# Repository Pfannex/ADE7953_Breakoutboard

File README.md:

# ADE7953 MQTT Wattmeter

Der ADE7953 wird über einen ESP8266-WLAN-Controller per I²C angesteuert.
Aktuell gibt es nur ein Breakoutboard mit Grundbeschaltung. 
Die Ankopplung der Leistungsmessgrößen erfolgt zu einem späteren Zeitpunkt.

***

- **ADE7953**
  - [Kalibrierung](https://github.com/Pfannex/ADE7953_Breakoutboard/wiki/Kalibrierung-%7C-ADE7953-MQTT-Wattmeter)
- **Firmware**
  - [ESP8266-Web-Interface](https://github.com/Pfannex/ADE7953_Breakoutboard/wiki/ESP8266-Web-Interface-%7C-ADE7953-MQTT-Wattmeter)
  - [MQTT](https://github.com/Pfannex/ADE7953_Breakoutboard/wiki/MQTT-%7C-ADE7953-MQTT-Wattmeter)
  - [FileSystem](https://github.com/Pfannex/ADE7953_Breakoutboard/wiki/FileSystem-%7C-ADE7953-MQTT-Wattmeter)
  - [OTA](https://github.com/Pfannex/ADE7953_Breakoutboard/wiki/OTA-%7C-ADE7953-MQTT-Wattmeter)
- **FHEM**
  - [FHEM](https://github.com/Pfannex/ADE7953_Breakoutboard/wiki/FHEM-%7C-ADE7953-MQTT-Wattmeter)  
  
***
[ToDo](https://github.com/Pfannex/ADE7953_Breakoutboard/blob/master/ToDo.md)

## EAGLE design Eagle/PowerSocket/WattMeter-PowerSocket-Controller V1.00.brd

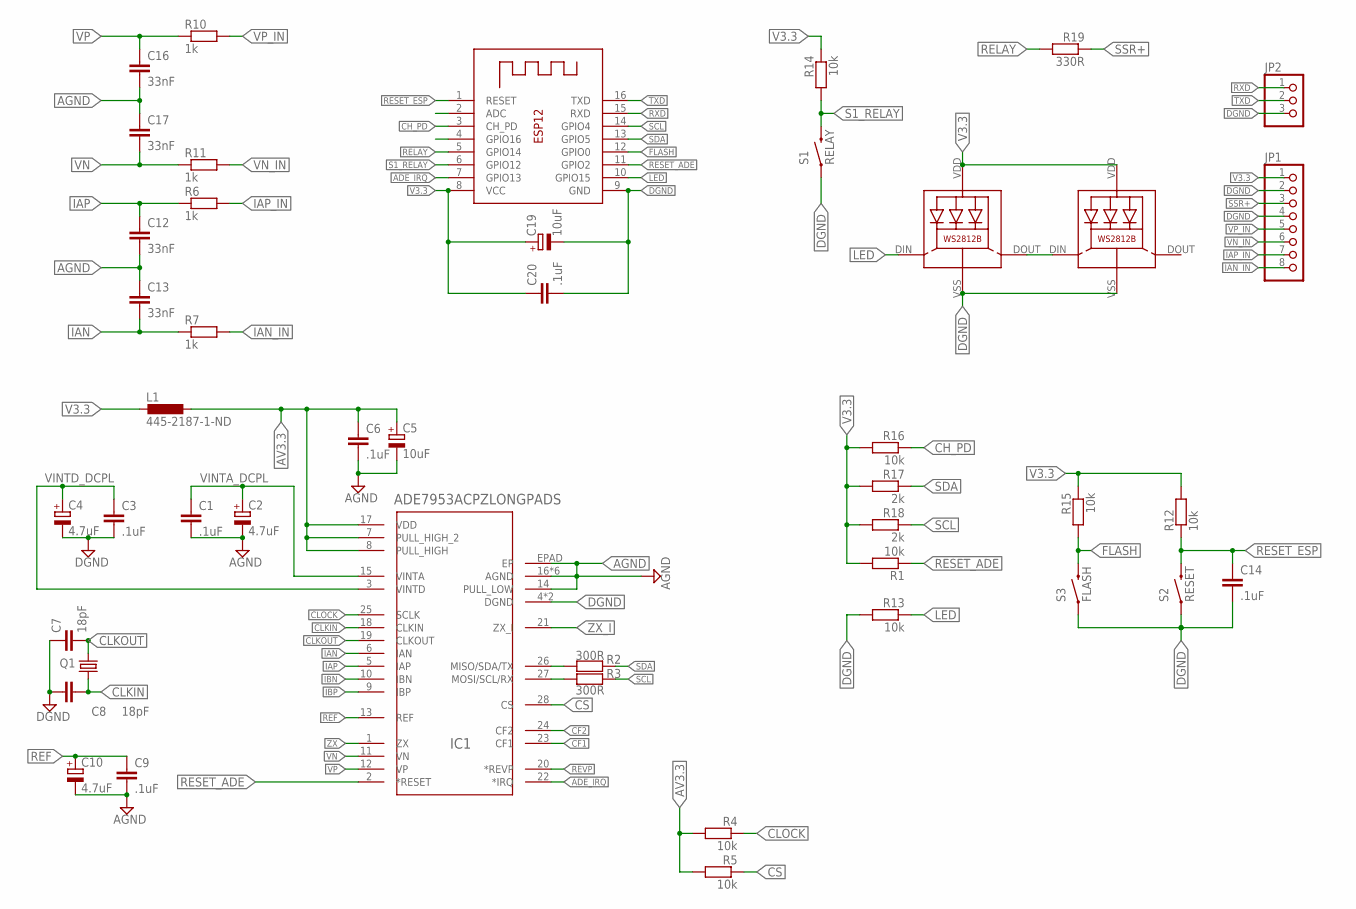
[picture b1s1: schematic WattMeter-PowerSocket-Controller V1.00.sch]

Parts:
C1, C3, C6, C9, C14, C20: .1uF; C0805K@1
C2, C4, C10: 4.7uF; A/3216-18R
C5, C19: 10uF; A/3216-18R
C7, C8: 18pF; C0805K@1
C12, C13, C16, C17: 33nF; C0805K@1
IC1: ADE7953ACPZLONGPADS; VQFN-28-D
JP1: PINHD-1X8; 1X08
JP2: PINHD-1X3; 1X03
L1: 445-2187-1-ND; L2012C
LED1, LED2: WS2812B
Q1: 535-10200-1-ND; SM49
R1, R4, R5, R12, R13, R14, R15, R16: 10k; R0805@1
R2, R3: 300R; R0805@1
R6, R7, R10, R11: 1k; R0805@1
R17, R18: 2k; R0805@1
R19: 330R; R0805@1
S1: RELAY; TACTILE-SWITCH-SMD
S2: RESET; TACTILE-SWITCH-1101NE
S3: FLASH; TACTILE-SWITCH-1101NE
X1: ESP-12

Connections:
ADC: X1.2 (ADC)
ADE_IRQ: IC1.22 (*IRQ), X1.7 (GPIO13)
AGND: C1.2, C2.-, C5.-, C6.2, C9.2, C10.-, C12.2, C13.1, C16.2, C17.1, IC1.14 (PULL_LOW), IC1.16 (AGND), IC1.29 (AGND), IC1.30 (AGND), IC1.31 (AGND), IC1.32 (AGND), IC1.EPAD (EP), IC1._AGND (AGND)
AV3.3: C5.+, C6.1, IC1.7 (PULL_HIGH_2), IC1.8 (PULL_HIGH), IC1.17 (VDD), L1.1, R4.2, R5.2
CF1: IC1.23 (CF1)
CF2: IC1.24 (CF2)
CH_PD: R16.1, X1.3 (CH_PD)
CLKIN: C8.2, IC1.18 (CLKIN), Q1.1
CLKOUT: C7.2, IC1.19 (CLKOUT), Q1.2
CLOCK: IC1.25 (SCLK), R4.1
CS: IC1.28 (CS), R5.1
DGND: C3.2, C4.-, C7.1, C8.1, C14.2, C19.-, C20.2, IC1.4 (DGND), IC1._DGND (DGND), JP1.2, JP1.4, JP2.3, LED1.VSS (GND), LED2.VSS (GND), R13.2, S1.1, S2.1, S3.1, X1.9 (GND)
FLASH: R15.2, S3.2, X1.12 (GPIO0)
GPIO16: X1.4 (GPIO16)
IAN: C13.2, IC1.6 (IAN), R7.1
IAN_IN: JP1.8, R7.2
IAP: C12.1, IC1.5 (IAP), R6.1
IAP_IN: JP1.7, R6.2
IBN: IC1.10 (IBN)
IBP: IC1.9 (IBP)
LED: LED1.DIN (DI), R13.1, X1.10 (GPIO15)
unnamed: LED1.DOUT (DO), LED2.DIN (DI)
REF: C9.1, C10.+, IC1.13 (REF)
RELAY: R19.2, X1.5 (GPIO14)
RESET_ADE: IC1.2 (*RESET), R1.1, X1.11 (GPIO2)
RESET_ESP: C14.1, R12.1, S2.2, X1.1 (RESET)
REVP: IC1.20 (*REVP)
RXD: JP2.1, X1.15 (RXD)
S1_RELAY: R14.2, S1.3 (2), X1.6 (GPIO12)
SCL: R3.2, R18.1, X1.14 (GPIO4)
SCL_: IC1.27 (MOSI/SCL/RX), R3.1
SDA: R2.2, R17.1, X1.13 (GPIO5)
SDA_: IC1.26 (MISO/SDA/TX), R2.1
SSR+: JP1.3, R19.1
TXD: JP2.2, X1.16 (TXD)
V3.3: C19.+, C20.1, JP1.1, L1.2, LED1.VDD, LED2.VDD, R1.2, R12.2, R14.1, R15.1, R16.2, R17.2, R18.2, X1.8 (VCC)
VINTA_DCPL: C1.1, C2.+, IC1.15 (VINTA)
VINTD_DCPL: C3.1, C4.+, IC1.3 (VINTD)
VN: C17.2, IC1.11 (VN), R11.1
VN_IN: JP1.6, R11.2
VP: C16.1, IC1.12 (VP), R10.1
VP_IN: JP1.5, R10.2
ZX: IC1.1 (ZX)
ZX_I: IC1.21 (ZX_I)

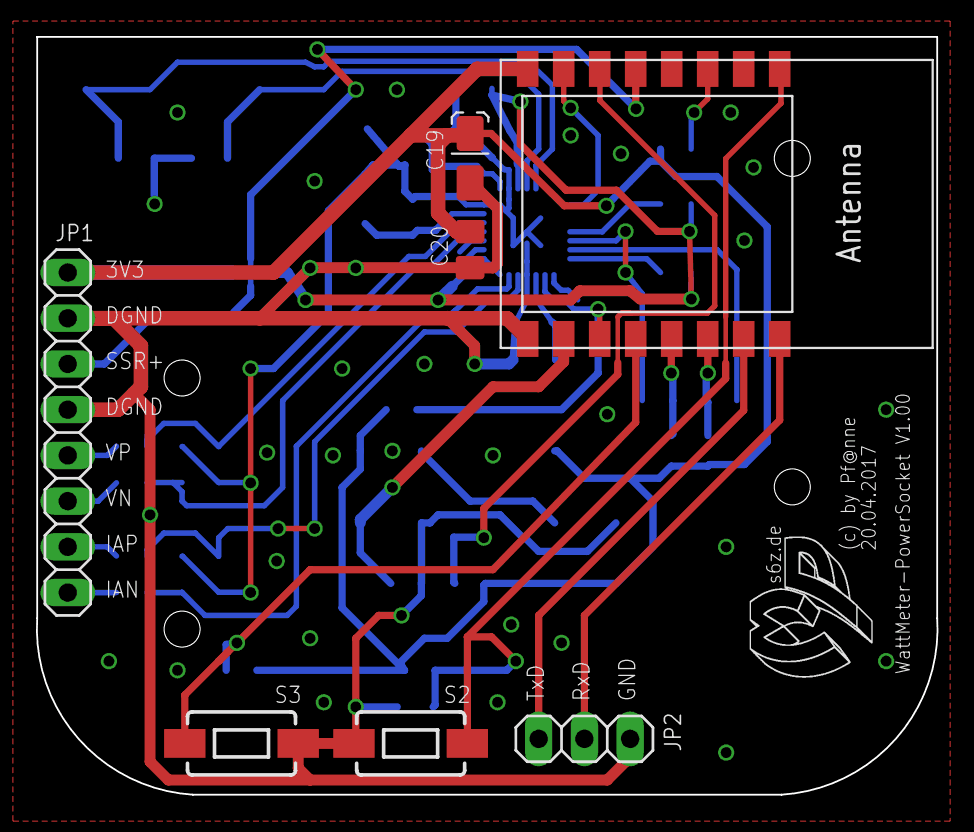
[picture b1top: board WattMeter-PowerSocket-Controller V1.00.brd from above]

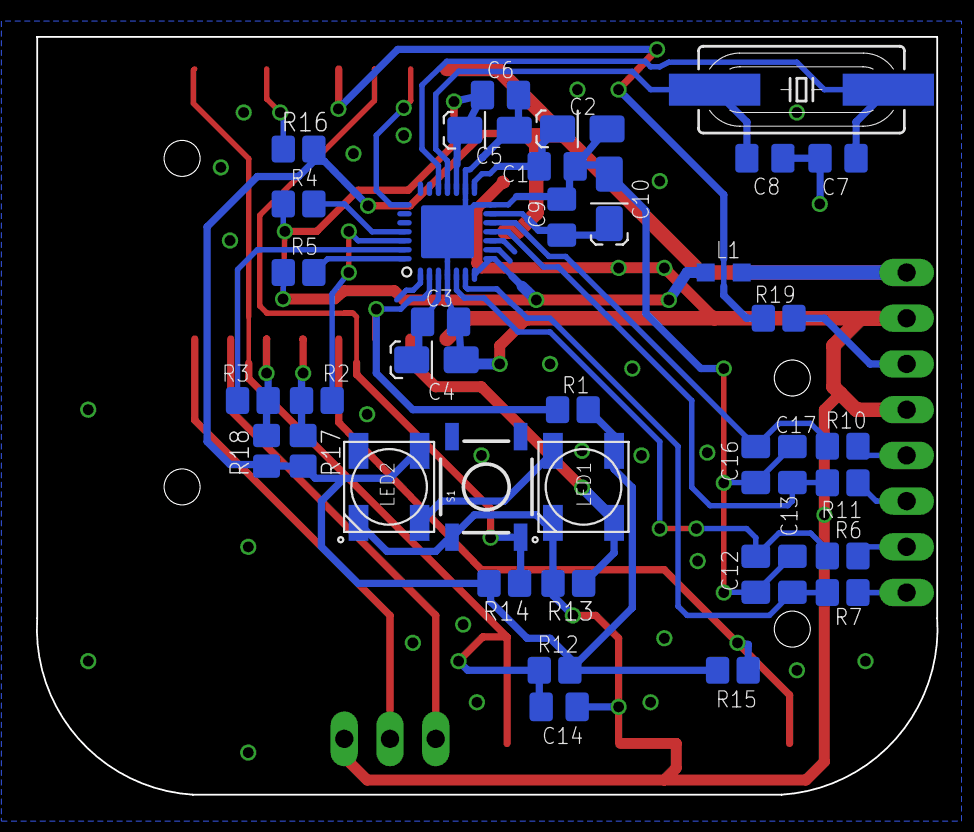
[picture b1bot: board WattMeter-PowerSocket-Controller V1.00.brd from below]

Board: 2 copper layers, 50.0 x 42.1 mm, 45 parts (38 on the bottom side), 35 nets.

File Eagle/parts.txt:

Partlist

Exported from ADE7953_WattMeter_breakout_v1.00.sch at 13.11.2016 07:56

EAGLE Version 7.7.0 Copyright (c) 1988-2016 CadSoft

Assembly variant: 

Part     Value               Device            Package    Library   Sheet

C1       .1uF                C-EUC0805K        C0805K@1   resistor  1
C2       4.7uF               CPOL-EUA/3216-18R A/3216-18R resistor  1
C3       .1uF                C-EUC0805K        C0805K@1   resistor  1
C4       4.7uF               CPOL-EUA/3216-18R A/3216-18R resistor  1
C5       10uF                CPOL-EUA/3216-18R A/3216-18R resistor  1
C6       .1uF                C-EUC0805K        C0805K@1   resistor  1
C7       18pF                C-EUC0805K        C0805K@1   resistor  1
C8       18pF                C-EUC0805K        C0805K@1   resistor  1
C9       .1uF                C-EUC0805K        C0805K@1   resistor  1
C10      4.7uF               CPOL-EUA/3216-18R A/3216-18R resistor  1
C11      1µF                 C-EUC0805K        C0805K@1   resistor  1
C12      33nF                C-EUC0805K        C0805K@1   resistor  1
C13      33nF                C-EUC0805K        C0805K@1   resistor  1
C14      33nF                C-EUC0805K        C0805K@1   resistor  1
C15      33nF                C-EUC0805K        C0805K@1   resistor  1
C16      33nF                C-EUC0805K        C0805K@1   resistor  1
C17      33nF                C-EUC0805K        C0805K@1   resistor  1
IC1      ADE7953ACPZLONGPADS ADE7953ACPZ5.0    VQFN-28-D  ade7953-2 1
JP1                          PINHD-1X14        1X14       pinhead   1
JP2                          PINHD-1X14        1X14       pinhead   1
JP3                          PINHD-1X2         1X02       pinhead   1
L1       445-2187-1-ND       L-EUL2012C        L2012C     resistor  1
Q1       535-10200-1-ND      CRYSTALSM49       SM49       crystal   1
R1       10k                 R-US_R0805        R0805@1    resistor  1
R2       300R                R-US_R0805        R0805@1    resistor  1
R3       300R                R-US_R0805        R0805@1    resistor  1
R4       10k                 R-US_R0805        R0805@1    resistor  1
R5       10k                 R-US_R0805        R0805@1    resistor  1
R6       1k                  R-US_R0805        R0805@1    resistor  1
R7       1k                  R-US_R0805        R0805@1    resistor  1
R8       1k                  R-US_R0805        R0805@1    resistor  1
R9       1k                  R-US_R0805        R0805@1    resistor  1
R10      1k                  R-US_R0805        R0805@1    resistor  1
R11      1k                  R-US_R0805        R0805@1    resistor  1
R12      10k                 R-US_R0805        R0805@1    resistor  1
R13      10k                 R-US_R0805        R0805@1    resistor  1
R14      10k                 R-US_R0805        R0805@1    resistor  1
R15      10k                 R-US_R0805        R0805@1    resistor  1
R16      10k                 R-US_R0805        R0805@1    resistor  1

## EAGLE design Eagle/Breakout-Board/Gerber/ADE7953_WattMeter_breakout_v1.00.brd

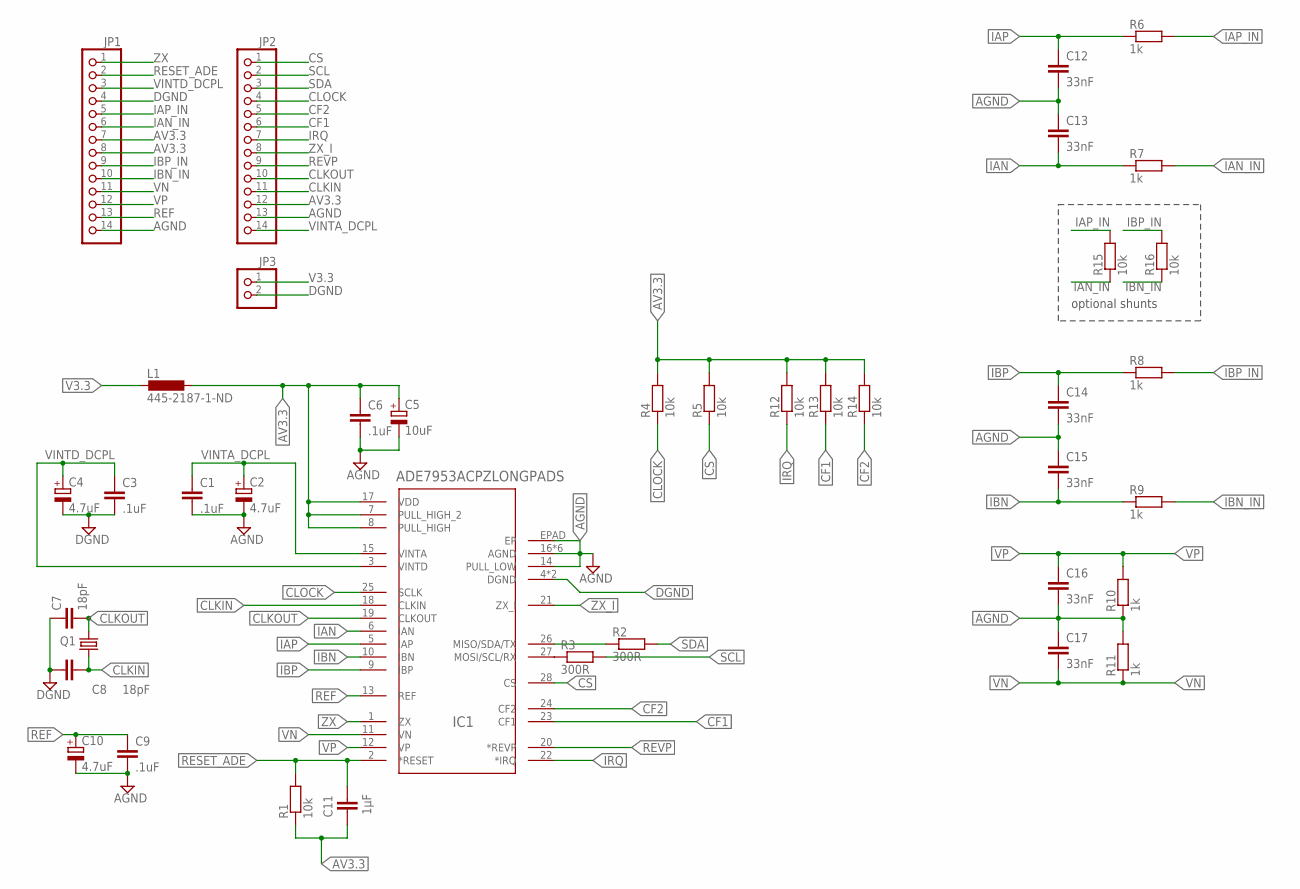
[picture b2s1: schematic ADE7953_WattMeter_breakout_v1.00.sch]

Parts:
C1, C3, C6, C9: .1uF; C0805K@1
C2, C4, C10: 4.7uF; A/3216-18R
C5: 10uF; A/3216-18R
C7, C8: 18pF; C0805K@1
C11: 1µF; C0805K@1
C12, C13, C14, C15, C16, C17: 33nF; C0805K@1
IC1: ADE7953ACPZLONGPADS; VQFN-28-D
JP1, JP2: PINHD-1X14; 1X14
JP3: PINHD-1X2; 1X02
L1: 445-2187-1-ND; L2012C
Q1: 535-10200-1-ND; SM49
R1, R4, R5, R12, R13, R14, R15, R16: 10k; R0805@1
R2, R3: 300R; R0805@1
R6, R7, R8, R9, R10, R11: 1k; R0805@1

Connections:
AGND: C1.2, C2.-, C5.-, C6.2, C9.2, C10.-, C12.2, C13.1, C14.2, C15.1, C16.2, C17.1, IC1.14 (PULL_LOW), IC1.16 (AGND), IC1.29 (AGND), IC1.30 (AGND), IC1.31 (AGND), IC1.32 (AGND), IC1.EPAD (EP), IC1._AGND (AGND), JP1.14, JP2.13, R10.1, R11.2
AV3.3: C5.+, C6.1, C11.2, IC1.7 (PULL_HIGH_2), IC1.8 (PULL_HIGH), IC1.17 (VDD), JP1.7, JP1.8, JP2.12, L1.1, R1.1, R4.2, R5.2, R12.2, R13.2, R14.2
CF1: IC1.23 (CF1), JP2.6, R13.1
CF2: IC1.24 (CF2), JP2.5, R14.1
CLKIN: C8.2, IC1.18 (CLKIN), JP2.11, Q1.1
CLKOUT: C7.2, IC1.19 (CLKOUT), JP2.10, Q1.2
CLOCK: IC1.25 (SCLK), JP2.4, R4.1
CS: IC1.28 (CS), JP2.1, R5.1
DGND: C3.2, C4.-, C7.1, C8.1, IC1.4 (DGND), IC1._DGND (DGND), JP1.4, JP3.2
IAN: C13.2, IC1.6 (IAN), R7.1
IAN_IN: JP1.6, R7.2, R15.1
IAP: C12.1, IC1.5 (IAP), R6.1
IAP_IN: JP1.5, R6.2, R15.2
IBN: C15.2, IC1.10 (IBN), R9.1
IBN_IN: JP1.10, R9.2, R16.1
IBP: C14.1, IC1.9 (IBP), R8.1
IBP_IN: JP1.9, R8.2, R16.2
IRQ: IC1.22 (*IRQ), JP2.7, R12.1
PIN26_MISO_SDA_TX: IC1.26 (MISO/SDA/TX), R2.1
PIN27_MOSI_SCL_RX: IC1.27 (MOSI/SCL/RX), R3.1
REF: C9.1, C10.+, IC1.13 (REF), JP1.13
RESET_ADE: C11.1, IC1.2 (*RESET), JP1.2, R1.2
REVP: IC1.20 (*REVP), JP2.9
SCL: JP2.2, R3.2
SDA: JP2.3, R2.2
V3.3: JP3.1, L1.2
VINTA_DCPL: C1.1, C2.+, IC1.15 (VINTA), JP2.14
VINTD_DCPL: C3.1, C4.+, IC1.3 (VINTD), JP1.3
VN: C17.2, IC1.11 (VN), JP1.11, R11.1
VP: C16.1, IC1.12 (VP), JP1.12, R10.2
ZX: IC1.1 (ZX), JP1.1
ZX_I: IC1.21 (ZX_I), JP2.8

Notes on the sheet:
optional shunts

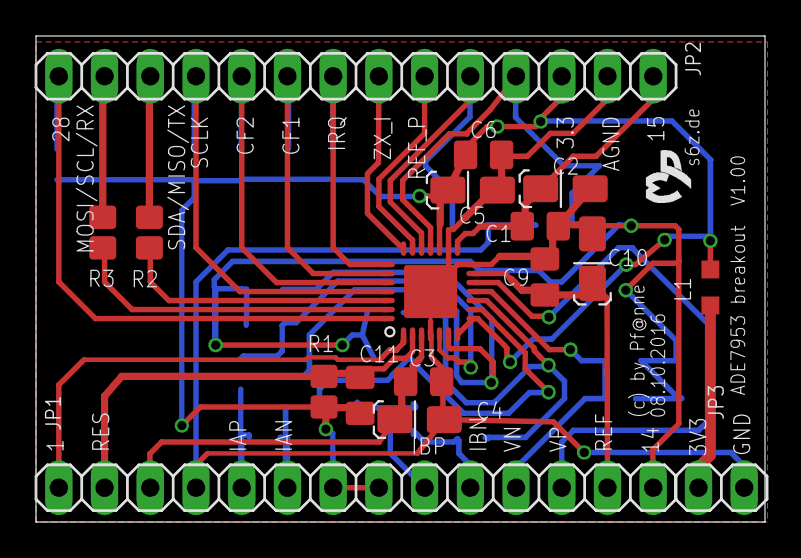
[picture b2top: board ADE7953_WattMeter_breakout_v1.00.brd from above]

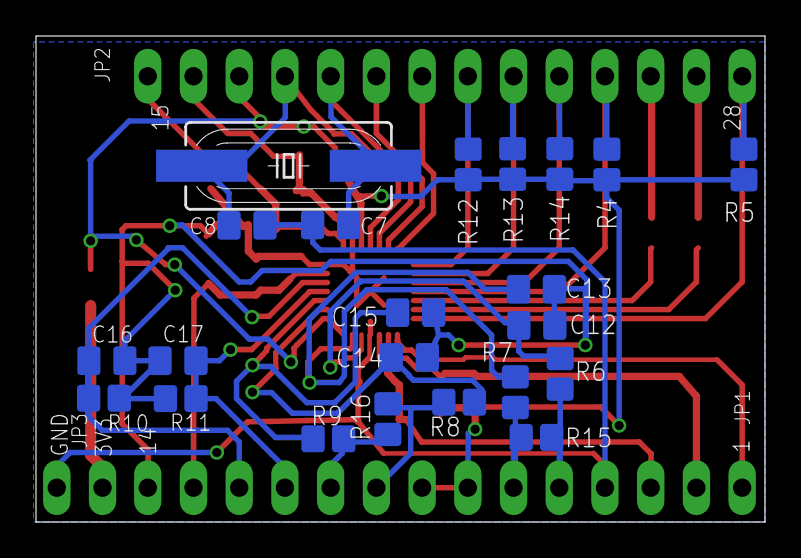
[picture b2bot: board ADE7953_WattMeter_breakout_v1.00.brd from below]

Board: 2 copper layers, 40.5 x 27.0 mm, 39 parts (22 on the bottom side), 32 nets.

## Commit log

2016-11-13 :circus_tent: Added .gitattributes & .gitignore files
2016-11-13 Upload
2016-11-13 Clean
2016-11-24 Upload ADE7953
2016-11-26 First SystemCheck
2016-12-03 alpha V0.200
2016-12-05 add JSON-File for ADE7953 Register saving
2016-12-10 save
2016-12-11 Sicherung
2016-12-11 Revert "save"
    This reverts commit 7f53961af1482455b5bff8486c0d0f5bdfaa4c04.
2016-12-12 Revert "Sicherung"
    This reverts commit ada358c9a5af75ba09b521207622b9de847316d1.
2016-12-12 Revert "Revert "Sicherung""
    This reverts commit 3015aaa5b434ddf9bc3df660cf9f371366c2f986.
2016-12-12 Registerstruct working
2016-12-13 new Upload
2016-12-13 add MQTT RW by register name
2016-12-14 test pic
2016-12-14 upload pics
2017-01-08 update measurement polling
2017-01-11 ensure V_INST is returned as double
2017-01-12 edit measurement
2017-01-13 TEST update
2017-01-13 set ADE7953 Register default values
2017-01-14 Update Measurement
2017-01-14 BugFixing MQTT-SaveConfig
2017-01-15 update instantaneous measurement
2017-01-18 Update
    INST V,IA,IB.... OK
    P,Q,S power measurement.... OK
    Excel calibration sheet.... OK
2017-01-18 Update Pics
2017-01-18 Pics
2017-01-21 Update ANGLE calc
2017-01-21 add Energy measurement / at Work
2017-01-22 Results of code review and optimization trials
2017-01-22 Pull from Boris
2017-01-22 update NTP
2017-01-22 FHEM sample configuration added
2017-01-22 modify I2C
2017-01-23 I2C write not working
2017-01-23 I2C r/w Test
2017-01-23 I2C read up to 800kHz
2017-01-24 update Excel-Sheet
2017-01-25 Energy measurement working!
2017-01-28 k-Faktor
2017-01-29 pushbutton functionality added
2017-01-30 update INST/100
2017-01-30 INST - 80ms/3kHz
2017-01-30 add getWaves
2017-02-01 getWaves 240 Samples@3kHz
2017-02-03 INST good working
2017-02-03 INST endless with 0,32kHz
2017-02-04 Relay added to peripherals, Blink mode added to LED
2017-02-04 more samples mor performance
2017-02-05 alphaV0.450 - almost ready
2017-02-12 speeUP getWaves
2017-02-13 add MQTT relay control
2017-02-18 TEMP relay
2017-02-24 save not working!
2017-02-26 update - still problems
2017-03-04 last update 21:17h
2017-03-05 alphaV0.500
2017-03-05 alphaV0.501
2017-03-19 Updated FHEM configuration file samples
2017-04-16 ADD WS2812B
2017-04-16 Update Eagle PowerSocket
